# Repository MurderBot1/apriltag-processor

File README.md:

# AprilTag camera: custom vision chip + 120 fps global-shutter camera, one USB-C cable

A self-contained camera that detects AprilTags (tag36h11) at **1280x800 / 120 fps** and hands back the **camera's pose
in a world frame you define**. You send it the tags you use and where they are (plus the lens calibration) once; it
stores them in flash and then streams the camera position and orientation over the same USB-C cable that powers it.

```
OV9281 (MIPI, 120 fps) -> ECP5 LFE5U-25F FPGA running custom RTL (threshold, despeckle, labelling, frame streamer) -> 8-bit frame bus ->
                          RP2350 MCU (tag decoder in C, pose solve, USB, stored field map) -> host
```

Nothing here is a stock vision pipeline: the per-pixel work is **hardware designed in Verilog in this repo**, the per-tag work (sub-pixel
corner fitting, tag36h11 decoding) is C code in this repo that runs on the MCU on the binary frame the FPGA streams to it (architecture "A3",
`docs/costdown.md`; it started life as a custom FPGA processor, the TPU, kept in `ref/tpu` as the bit-exact reference). The host only sees the tag
estimates and poses, never an image.

## What is in the box

| directory | contents |
|---|---|
| `rtl/` | the chip: D-PHY + CSI-2 receiver, adaptive threshold, despeckle, connected components, the MCU frame streamer (`mask_stream`), SPI/I2C, top levels, pin constraints (`apriltag_cam.lpf`) |
| `tools/` | golden Python models of every block, TPU assembler + instruction-set simulator + the program (`tpu_prog.py`, the golden model of `firmware/core/attpu.c`), Cortex-M33 timing estimators (`m33_cycles.py`, `m33_pose_cycles.py`, `frame_budget.py`), Blender scene/dataset generator, reference detector, sensor init generator, FPGA flow scripts |
| `tb/`, `tests/` | Verilog testbenches and 226 pytest tests (see `docs/verification.md`) |
| `test_images/` | **100 rendered 1280x800 test frames in 10 categories of 10** (normal, bright, dark, low-contrast, gradient light, shadow, noise, clutter, blur, perspective; Blender Cycles, lens distortion + sensor noise model) with ground-truth poses (`ground_truth.json`) |
| `firmware/core`, `firmware/rp2350` | MCU firmware: pose solver, USB protocol, flash storage, auto exposure; RP2350 (Pico SDK) port |
| `host/` | Python library + CLI (`atcam.py`) with a simulated device so everything runs without hardware |
| `pcb/` | 4-layer 48 x 48 mm board generated from code (`design.py`, `build_pcb.py`), routed, fabrication outputs |
| `housing/` | 3D-printable two-part enclosure (OpenSCAD, STLs) |
| `docs/` | architecture, hardware, protocol, verification, FPGA results |
| `config/` | example field map (`tag_map.json`) and camera calibration |

## Using it

```python
import sys; sys.path.insert(0, "host")
from apriltag_cam import Camera, load_json
with Camera.open_serial("COM5") as cam:               # USB-C CDC serial port
    cam.set_calibration(load_json("config/camera_calibration.json"))
    cam.set_field(load_json("config/tag_map.json"))   # tag ids, sizes, 3D positions + orientations (quaternion wxyz)
    cam.commit()                                      # stored in flash; survives power cycles
    for pose in cam.stream():                         # ~120 Hz
        print(pose.frame_id, pose.position, pose.quaternion, pose.ntags, pose.rms_px)
```
`py -3.12 host/atcam.py --sim configure --map config/tag_map.json --calib config/camera_calibration.json` and `... --sim stream` run the same flow against the simulated device (native firmware + a fake FPGA fed with real RTL results).
Protocol: `docs/protocol.md`. Conventions (world, tag, camera frames, corner order) are at the top of `tools/geom.py`.

## Rebuilding / re-running

```
py -3.12 tools/make_tags.py               # tag images + the 587-code ROM table
py -3.12 tools/make_dataset_100.py        # the 100-image dataset: Blender renders (needs Blender 5.x) -> test_images/ (deterministic, see docs/verification.md)
py -3.12 tools/tpu_prog.py                # assemble the reference TPU program (ref/tpu/tpu_prog.hex)
py -3.12 tools/m33_cycles.py              # run time of the C tag unit on a Cortex-M33 (Unicorn + cycle model)
py -3.12 tests/run_all.py                 # the whole verification suite
bash tools/fpga_flow.sh                   # yosys + nextpnr-ecp5 (+ ecppack bitstream), default device 25k = shipping LFE5U-25F; FPGA_DEVICE=45k|85k for experiments
"C:/Program Files/KiCad/10.0/bin/python.exe" pcb/build_pcb.py --route ; py -3.12 pcb/make_outputs.py
```
Tools used: Icarus Verilog 13, Yosys 0.66, nextpnr-ecp5 0.7, KiCad 10, Freerouting 2.1, OpenSCAD 2021, Blender 5.1,
arm-none-eabi-gcc, Pico SDK (all installed during the build; see `docs/`).

## Build and release (deploy)

`bash tools/build_all.sh [--strict] [--skip-tests] [--skip-fpga]` builds every buildable output into `products/` (git-ignored) and writes
`products/MANIFEST.json` / `MANIFEST.txt` (commit, build date, tool versions, per-step ok/skipped/failed with notes, and file name, size and sha256).
Products: FPGA bitstream + netlist/config + timing/utilisation reports (yosys, nextpnr-ecp5, ecppack), RP2350 firmware (`.uf2/.elf/.bin`, needs
arm-none-eabi-gcc + Pico SDK via `PICO_SDK_PATH`), native firmware-sim library, host bundle + configs, Python wheel, C++ static lib + headers,
Java jar, Rust `.crate`/rlib, docs tarball and the committed PCB gerbers/BOM (copied, not regenerated; needs KiCad). A step whose toolchain is
missing is recorded as `skipped` in the manifest (never faked); set `REQUIRE="fpga firmware ..."` to make that an error. The FPGA flow targets the shipping part LFE5U-25F-8BG381I by default (nextpnr `--25k --package CABGA381 --speed 8`; `FPGA_DEVICE`/`FPGA_SPEED` override for experiments). The manifest has an `fpga` block (device, speed, package, part) and `fpga/summary.txt` states it. A timing miss for every seed in `FPGA_SEEDS`, or a bitstream for any other device or speed, is recorded as `failed` (the bitstream is still produced; `FPGA_ALLOW_NONSHIPPING=1` downgrades the device check to a warning for experiments).

**RP2350 firmware image.** Build on Linux (the Windows msys `ld` 2.47 fails the Pico SDK link with "pico_flash_region.ld appears multiple times", so
Windows is not a supported firmware build host). Needs `gcc-arm-none-eabi` (CI: Ubuntu 24.04 package, 13.2.1), `libnewlib-arm-none-eabi`, `cmake`, `ninja` and
Pico SDK **2.1.1** with submodules (tinyusb); the SDK builds picotool from source on first configure (network needed):
```
git clone --depth 1 --branch 2.1.1 --recurse-submodules --shallow-submodules https://github.com/raspberrypi/pico-sdk.git ~/pico-sdk
cmake -S firmware/rp2350 -B build/rp2350 -G Ninja -DPICO_SDK_PATH=~/pico-sdk && cmake --build build/rp2350
python3 tools/fw_size.py build/rp2350/apriltag_cam.elf --bin build/rp2350/apriltag_cam.bin --uf2 build/rp2350/apriltag_cam.uf2
```
The workflow `.github/workflows/firmware.yml` does this on every pull request that touches `firmware/`, checks the `.uf2` structure, uploads
`apriltag_cam.uf2/.elf/.bin/.elf.map` as the artifact `rp2350-firmware` and posts the size report (flash image vs 16 MB, static SRAM vs 520 KB) on the PR.
It never creates a release. Flash the `.uf2` by holding BOOTSEL while plugging in USB and copying the file to the `RP2350` drive (not yet tried on hardware).

**Releasing:** pushing to the `deploy` branch (`git push origin main:deploy`, or merge `main` into `deploy`) runs `.github/workflows/release.yml`.
It installs the toolchains, runs `tools/build_all.sh --strict`, uploads `products/` as a workflow artifact, and creates a NEW GitHub Release
tagged `deploy-<run_number>-<short sha>` with the products and manifest attached and notes listing the commit, date, tool versions and
build/test results. Earlier releases are never overwritten. `main` does not trigger releases. The workflow can also be started manually
(workflow_dispatch) from any ref; the manual run has a `dry_run` input (default true) that does everything except `gh release create`
(it still lists the assets and checks that `firmware_apriltag_cam.uf2/.elf` are present). A "Verify the build targets the shipping design" step fails the release unless the FPGA is 25k / CABGA381 / speed 8 with timing met, the uf2 exists, `products/docs/bom.csv` equals `pcb/output/bom.csv` with U1 = LFE5U-25F-8BG381I, and the committed PCB carries that part. It uses `GITHUB_TOKEN` with `contents: write`.

## Headline results (details and caveats in `docs/verification.md`, `docs/fpga.md`, `docs/hardware.md`)

* **120.08 fps** sustained in full-chip simulation at true sensor timing (832,800 clocks per frame at 100 MHz), every frame leaves the FPGA
  as a complete packet; the MCU has two frame buffers so capture never stalls.
* 100 rendered frames (10 conditions x 10, rendered for the shipping lens: CIL023, 82.2 degrees HFOV, fx 733 px, -5 % TV distortion) through the simulated chip + the MCU's solver: **median camera position error about
  1-5 mm and 0.03-0.17 deg per category** where tags are found; **88 % of the detectable tags overall (501 / 570; the reference AprilTag library: 98 %)**,
  100 % on dark / grad / noise / normal, 99 % bright, 92-94 % clutter / blur / persp, 90 % shadow, but still
  **2 % on the low-contrast category** with the reset THRESH ratio (54 / 54 with ratio 1, chosen automatically by the firmware), see `docs/verification.md`.
* GitHub Actions: one check per dataset category (`N/10 detected`, reference detector) plus an all-tests workflow, see `docs/verification.md`.
* RTL is verified bit-exact against Python golden models (threshold, despeckle, labelling), the C tag unit bit-exact against the golden model of the old FPGA processor, and the whole
  chain is exercised with real CSI-2 packets and a bit-level D-PHY model with lane skew and clock offsets.
* Open-source place-and-route onto the real ECP5 CABGA-381 pins, shipping part LFE5U-25F-8BG381I: 13.4 k LUT4 (55 %), 56 of 56 block RAM (100 %, no margin), core clock closes 85.7 MHz and D-PHY 200 MHz on 7 of 7 seeds (nextpnr estimates, not signoff; `docs/fpga.md`). Earlier 45F numbers (12.2 k LUT4, 56 of 108 block RAM, 4 of 6 seeds, older RTL and tools) are kept in `docs/fpga.md`, labelled as 45F.

## Honest limits - read before building hardware

1. **Not run on silicon.** Everything is simulated or tool-checked; there is no physical board. The ECP5 D-PHY receiver
   (LVDS gearing, sync hunt) and the OV9281 bring-up are the first things to validate on a prototype.
2. **OV9281 footprint**: the ball map comes from an open-hardware reference design, but the CSP ball pitch/pad size
   is assumed (0.5 mm / 0.25 mm). Verify against OmniVision's drawing before ordering. Bare-CSP assembly with an
   M12 holder needs a specialist assembler.
3. **Timing closure**: see `docs/fpga.md` for the measured fmax of each clock domain against the 100 MHz / 200 MHz
   targets. Anything reported as failing there must be fixed (more pipelining) before relying on 120 fps in hardware.
4. Detection is weaker than the reference library at long range (> ~3.5 m for 16.5 cm tags), for low-contrast scenes (0 % on the
   `lowcon` category with the reset THRESH ratio; 100 % with ratio 2, see `results/lowcon_ratio.md`) and for small / grazing / shadowed tags. The labeller no longer rejects busy frames (256 runs/row, label recycling,
   the 64 largest candidates kept), but a cluttered or noisy frame costs the MCU up to about 9 ms (estimate, Cortex-M33 emulation, median 1.6 ms; the old FPGA processor
   needed up to 30 ms): in a stream at 120 fps a heavy frame can make the MCU miss a packet (`frames_dropped`); the model predicts 1 - 4 % of frames
   if every 10th frame were the slowest of its category (`results/frame_budget.md`; the old design: 20 %). The MCU timing, the PIO/DMA frame
   capture and the bus timing margin are **not measured on hardware**.
5. No schematic capture: the board is netlist-first (`pcb/design.py`, `pcb/output/netlist.txt`).

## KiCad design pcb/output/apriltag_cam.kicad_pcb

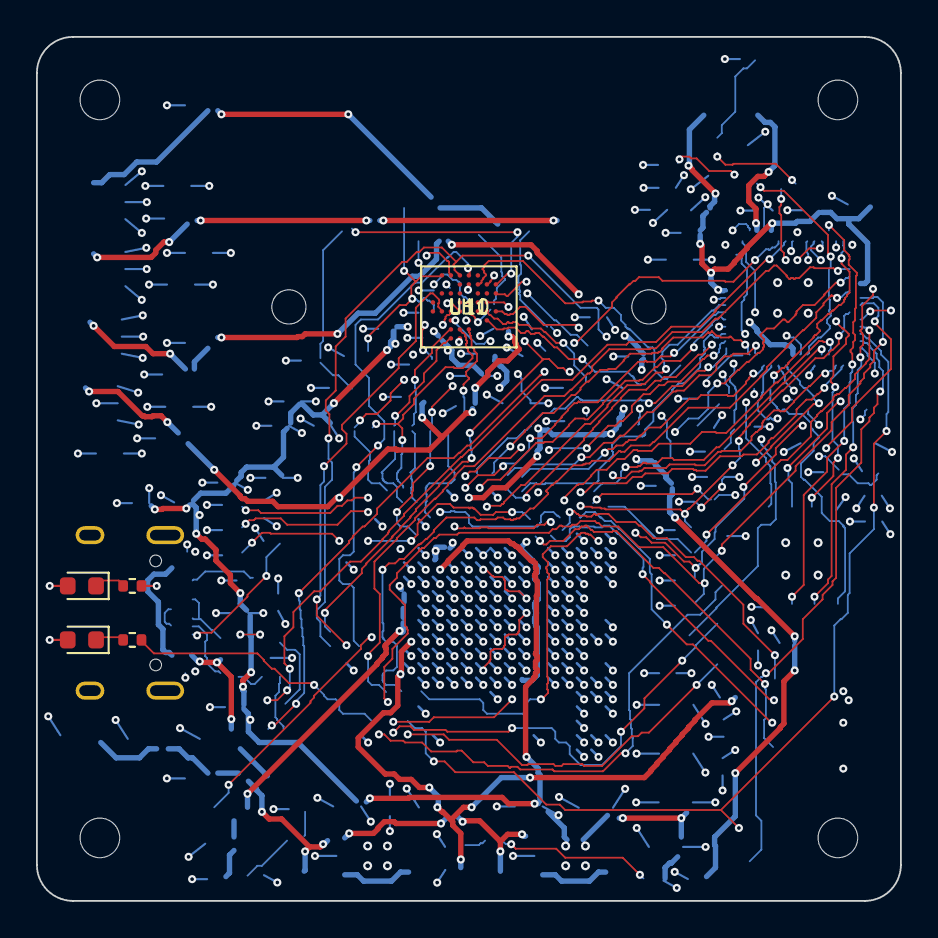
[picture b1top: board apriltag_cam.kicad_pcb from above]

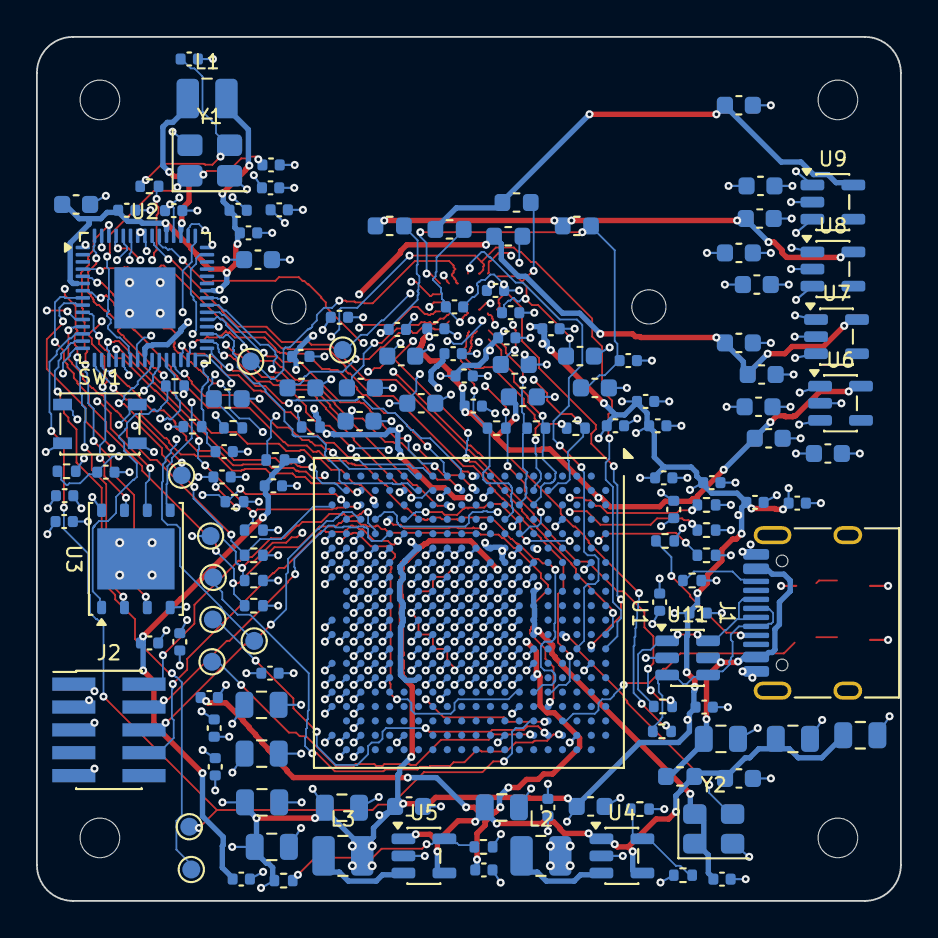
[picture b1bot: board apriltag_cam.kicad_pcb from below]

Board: 4 copper layers, 48.0 x 48.0 mm, 152 parts (142 on the bottom side), 95 nets.

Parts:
C1, C2, C3, C4, C5, C6, C7, C8, C9, C13, C14, C17, C38, C39, C40, C41, C42, C43, C44, C45, C46, C47, C48, C49, C50, C51, C52, C53, C54, C55, C56, C57, C58, C59, C60, C61, C62, C63, C64, C65, C70, C72, C74, C76, C77, C78: 100n; C_0402_1005Metric
C10, C11, C12, C36, C37, C66, C67, C68, C69: 4u7; C_0603_1608Metric
C15, C16: 15p; C_0402_1005Metric
C18, C19, C21, C24: 10u; C_0805_2012Metric
C20, C28, C30, C32, C34, C71, C73, C75, C79, C80, C81, C82: 1u; C_0603_1608Metric
C22, C23, C25, C26, C27: 22u; C_0805_2012Metric
C29, C31, C33, C35: 2u2; C_0603_1608Metric
D1: PWR; LED_0603_1608Metric
D2: STAT; LED_0603_1608Metric
FB1: BLM18 600R; L_0603_1608Metric
FB2, FB3, FB4, FB5, FB6: BLM18 120R; L_0603_1608Metric
J1: USB-C; USB_C_Receptacle_HRO_TYPE-C-31-M-12
J2: JTAG; PinHeader_2x05_P1.27mm_Vertical_SMD
L1: 3u3; L_1008_2520Metric
L2, L3: 2u2; L_1008_2520Metric
LH1: M12 holder 20x20; M12_LENS_MOUNT
MH1, MH2, MH3, MH4: M2; MountingHole_2.2mm_M2
R1, R2: 33R; R_0402_1005Metric
R3, R19, R20, R21, R22, R23: 10k; R_0402_1005Metric
R4, R5, R14, R15: 1k; R_0402_1005Metric
R6, R7: 5k1; R_0402_1005Metric
R8, R9: 27R; R_0402_1005Metric
R10: 453k; R_0402_1005Metric
R11, R13: 100k; R_0402_1005Metric
R12: 82k5; R_0402_1005Metric
R16, R17, R18: 4k7; R_0402_1005Metric
R24, R25, R26: 100R; R_0402_1005Metric
R27, R28: 2k2; R_0402_1005Metric
SW1: BOOTSEL; SW_SPST_PTS810
TP1: SWCLK; TestPoint_Pad_D1.0mm
TP2: SWDIO; TestPoint_Pad_D1.0mm
TP3: GND; TestPoint_Pad_D1.0mm
TP4: LED_1; TestPoint_Pad_D1.0mm
TP5: LED_2; TestPoint_Pad_D1.0mm
TP6: LED_3; TestPoint_Pad_D1.0mm
TP7: MCU_AUX; TestPoint_Pad_D1.0mm
TP8: FPGA_IRQ; TestPoint_Pad_D1.0mm
TP9: SNS_STROBE; TestPoint_Pad_D1.0mm
TP10: SNS_FSIN; TestPoint_Pad_D1.0mm
U1: LFE5U-25F-8BG381I; Lattice_caBGA-381_17x17mm_Layout20x20_P0.8mm
U2: RP2350A; QFN-60-1EP_7x7mm_P0.4mm_EP3.4x3.4mm
U3: W25Q128JVPIQ; WSON-8-1EP_6x5mm_P1.27mm_EP3.4x4.3mm
U4, U5: TLV62569; SOT-23-5
U6: ME6211C25; SOT-23-5
U7: TLV75518; SOT-23-5
U8: ME6211C28; SOT-23-5
U9: TLV75512; SOT-23-5
U10: OV9281; OV9281_CSP
U11: USBLC6-2SC6; SOT-23-6
Y1: 12MHz 10pF; Crystal_SMD_3225-4Pin_3.2x2.5mm
Y2: 24MHz 1.8V; Oscillator_SMD_Abracon_ASE-4Pin_3.2x2.5mm

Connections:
+1V1: C25.1, C26.1, C27.1, C38.1, C39.1, C40.1, C41.1, C42.1, C43.1, C44.1, C45.1, C46.1, C47.1, C48.1, C49.1, C66.1, C67.1, L3.2, R12.1, U1.H8, U1.H9, U1.H10, U1.H11, U1.H12, U1.H13, U1.J8, U1.J13, U1.K8, U1.K13, U1.L8, U1.L13, U1.M8, U1.M13, U1.N8, U1.N9, U1.N10, U1.N11, U1.N12, U1.N13
+1V1MCU: C7.1, C8.1, C9.1, C10.1, L1.2, U2.6, U2.23, U2.39, U2.50
+1V2: C35.1, FB3.1, FB5.1, U9.5
+1V8: C31.1, C37.1, C54.1, C55.1, C56.1, C57.1, C58.1, C70.1, FB4.1, R27.2, R28.2, U1.F9, U1.F10, U1.F11, U1.F12, U1.H6, U1.H7, U1.J6, U7.5, Y2.1, Y2.4
+2V5: C29.1, C50.1, C51.1, C52.1, C53.1, C68.1, U1.F6, U1.F15, U1.P6, U1.P15, U6.5
+2V8: C33.1, FB2.1, FB6.1, U8.5
+3V3: C1.1, C2.1, C3.1, C4.1, C5.1, C6.1, C11.1, C17.1, C22.1, C23.1, C28.1, C30.1, C32.1, C34.1, C36.1, C59.1, C60.1, C61.1, C62.1, C63.1, C64.1, C65.1, C69.1, D1.2, D2.2, J2.1, L2.2, R1.1, R2.1, R3.2, R10.1, R16.2, R19.2, R20.2, R21.2, R22.2, R23.2, U1.H14, U1.H15, U1.J15, U1.L6, U1.L7, U1.L14, U1.L15, U1.M6, U1.M15, U1.P9, U1.P10, U2.1, U2.11, U2.20, U2.30, U2.38, U2.45, U2.49, U2.53, U2.54, U3.8, U6.1, U6.3, U7.1, U7.3, U8.1, U8.3, U9.1, U9.3
+5V: C18.1, C20.1, C21.1, C24.1, FB1.2, U4.1, U4.4, U5.1, U5.4
ADC_AVDD: C13.1, R2.2, U2.44
AVDD_S: C71.1, C72.1, FB2.2, U10.B8
BOOT_N: R5.2, SW1.1
CC1: J1.A5, R6.1
CC2: J1.B5, R7.1
CFG0: R16.1, U1.U4
CFG1: R17.1, U1.T4
CFG2: R18.1, U1.R4
CLK24M: U1.D12, Y2.3
DOVDD_S: C75.1, C76.1, FB4.2, U10.B7
DVDD_S: C73.1, C74.1, FB3.2, U10.A2
EVDD_S: C78.1, FB6.2, U10.F3
FB_CLK: U1.K2, U2.36
FB_D0: U1.P1, U2.27
FB_D1: U1.N1, U2.28
FB_D2: U1.M1, U2.29
FB_D3: U1.L1, U2.31
FB_D4: U1.K1, U2.32
FB_D5: U1.P2, U2.33
FB_D6: U1.N2, U2.34
FB_D7: U1.L2, U2.35
FB_FS: U1.M3, U2.37
FPGA_CCLK: U1.U3, U2.18
FPGA_CFG_CS: U1.R2, U2.17
FPGA_CFG_MISO: U1.V2, U2.16
FPGA_CFG_MOSI: U1.W2, U2.19
FPGA_DONE: R21.1, U1.Y3, U2.12
FPGA_INITN: R20.1, U1.V3, U2.10
FPGA_IRQ: TP8.1, U1.F18, U2.13
FPGA_PROGRAMN: R19.1, U1.W3, U2.9
FPGA_RST: R22.1, U1.G16, U2.15
GND: C1.2, C2.2, C3.2, C4.2, C5.2, C6.2, C7.2, C8.2, C9.2, C10.2, C11.2, C12.2, C13.2, C14.2, C15.2, C16.2, C17.2, C18.2, C19.2, C20.2, C21.2, C22.2, C23.2, C24.2, C25.2, C26.2, C27.2, C28.2, C29.2, C30.2, C31.2, C32.2, C33.2, C34.2, C35.2, C36.2, C37.2, C38.2, C39.2, C40.2, C41.2, C42.2, C43.2, C44.2, C45.2, C46.2, C47.2, C48.2, C49.2, C50.2, C51.2, C52.2, C53.2, C54.2, C55.2, C56.2, C57.2, C58.2, C59.2, C60.2, C61.2, C62.2, C63.2, C64.2, C65.2, C66.2, C67.2, C68.2, C69.2, C70.2, C71.2, C72.2, C73.2, C74.2, C75.2, C76.2, C77.2, C78.2, C79.2, C80.2, C81.2, C82.2, J1.A1, J1.A12, J1.B1, J1.B12, J1.SH, J2.3, J2.5, J2.9, R6.2, R7.2, R11.2, R13.2, R14.2, R17.2, R18.2, SW1.2, TP3.1, U1.B7, U1.B14, U1.C19, U1.D4, U1.F7, U1.F8, U1.F13, U1.F14, U1.G4, U1.G6, U1.G7, U1.G8, U1.G9, U1.G10, U1.G11, U1.G12, U1.G13, U1.G14, U1.G15, U1.G17, U1.H19, U1.J2, U1.J7, U1.J9, U1.J10, U1.J11, U1.J12, U1.J14, U1.K6, U1.K7, U1.K9, U1.K10, U1.K11, U1.K12, U1.K14, U1.K15, U1.L9, U1.L10, U1.L11, U1.L12, U1.M2, U1.M7, U1.M9, U1.M10, U1.M11, U1.M12, U1.M14, U1.M16, U1.N6, U1.N7, U1.N14, U1.N15, U1.P7, U1.P8, U1.P11, U1.P12, U1.P13, U1.P14, U1.R19, U1.T6, U1.T7, U1.T8, U1.T9, U1.T10, U1.T11, U1.T12, U1.T13, U1.T14, U1.T15, U1.U6, U1.U7, U1.U8, U1.U9, U1.U10, U1.U11, U1.U12, U1.U13, U1.U14, U1.U15, U1.V5, U1.V6, U1.V7, U1.V8, U1.V9, U1.V10, U1.V11, U1.V12, U1.V13, U1.V14, U1.V15, U1.V16, U1.V17, U1.V18, U1.V19, U1.V20, U1.W6, U1.W7, U1.W12, U1.W15, U1.W16, U1.W19, U1.W20, U1.Y5, U1.Y6, U1.Y7, U1.Y8, U1.Y11, U1.Y12, U1.Y14, U1.Y15, U1.Y16, U1.Y17, U1.Y19, U2.47, U2.61, U3.4, U3.9, U4.2, U5.2, U6.2, U7.2, U8.2, U9.2, U10.A3, U10.C8, U10.E3, U11.2, Y1.2, Y1.4, Y2.2
JTAG_TCK: J2.4, U1.T5
JTAG_TDI: J2.8, U1.R5
JTAG_TDO: J2.6, U1.V4
JTAG_TMS: J2.2, U1.U5
LED_1: TP4.1, U1.D19
LED_2: TP5.1, U1.E19
LED_3: TP6.1, U1.F19
LED_PWR_K: D1.1, R14.1
LED_STAT: R15.1, U1.D18
LED_STAT_K: D2.1, R15.2
MCU_AUX: TP7.1, U2.14
MCU_RUN: C14.1, R3.1, U2.26
MIPI_CLK_N: R24.2, U1.E2, U10.H4
MIPI_CLK_P: R24.1, U1.F2, U10.G4
MIPI_D0_N: R25.2, U1.F3, U10.H3
MIPI_D0_P: R25.1, U1.G3, U10.G3
MIPI_D1_N: R26.2, U1.G5, U10.F5
MIPI_D1_P: R26.1, U1.H4, U10.G5
PVDD_S: C77.1, FB5.2, U10.D5
QSPI_SCLK: U2.56, U3.6
QSPI_SD0: U2.57, U3.5
QSPI_SD1: U2.59, U3.2
QSPI_SD2: U2.58, U3.3
QSPI_SD3: U2.55, U3.7
QSPI_SS: R5.1, U2.60, U3.1
SCL: R27.1, U1.A12, U10.E4
SDA: R28.1, U1.A13, U10.A4
SNS_FSIN: TP10.1, U10.B5
SNS_STROBE: TP9.1, U10.B6
SPI_CS: R23.1, U1.E17, U2.8
SPI_MISO: U1.F16, U2.7
SPI_MOSI: U1.E18, U2.5
SPI_SCK: U1.E16, U2.4
SW1V1: L3.1, U5.3
SW1V1_FB: R12.2, R13.1, U5.5
SW3V3: L2.1, U4.3
SW3V3_FB: R10.2, R11.1, U4.5
SWCLK: TP1.1, U2.24
SWDIO: TP2.1, U2.25
USB_DM_MCU: R9.2, U2.51
USB_DN: J1.A7, J1.B7, R9.1, U11.3, U11.4
USB_DP: J1.A6, J1.B6, R8.1, U11.1, U11.6
USB_DP_MCU: R8.2, U2.52
VBUS: C19.1, FB1.1, J1.A4, J1.A9, J1.B4, J1.B9, U11.5
VH: C79.1, U10.E8
VN1: C80.1, U10.D7
VN2: C81.1, U10.E7
VN3: C82.1, U10.F7
VREG_AVDD: C12.1, R1.2, U2.46
VREG_LX: L1.1, U2.48
XIN: C15.1, U2.21, Y1.1
XOUT: C16.1, R4.1, Y1.3
XOUT_R: R4.2, U2.22
XSHUTDN: U1.C13, U10.A5
XVCLK: U1.B13, U10.E2

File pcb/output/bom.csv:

Qty,Value,Footprint,References
46,100n,C_0402_1005Metric,C1 C2 C3 C4 C5 C6 C7 C8 C9 C13 C14 C17 C38 C39 C40 C41 C42 C43 C44 C45 C46 C47 C48 C49 C50 C51 C52 C53 C54 C55 C56 C57 C58 C59 C60 C61 C62 C63 C64 C65 C70 C72 C74 C76 C77 C78
9,4u7,C_0603_1608Metric,C10 C11 C12 C36 C37 C66 C67 C68 C69
2,15p,C_0402_1005Metric,C15 C16
4,10u,C_0805_2012Metric,C18 C19 C21 C24
12,1u,C_0603_1608Metric,C20 C28 C30 C32 C34 C71 C73 C75 C79 C80 C81 C82
5,22u,C_0805_2012Metric,C22 C23 C25 C26 C27
4,2u2,C_0603_1608Metric,C29 C31 C33 C35
1,PWR,LED_0603_1608Metric,D1
1,STAT,LED_0603_1608Metric,D2
1,BLM18 600R,L_0603_1608Metric,FB1
5,BLM18 120R,L_0603_1608Metric,FB2 FB3 FB4 FB5 FB6
1,USB-C,USB_C_Receptacle_HRO_TYPE-C-31-M-12,J1
1,JTAG,PinHeader_2x05_P1.27mm_Vertical_SMD,J2
1,3u3,L_1008_2520Metric,L1
2,2u2,L_1008_2520Metric,L2 L3
2,33R,R_0402_1005Metric,R1 R2
1,453k,R_0402_1005Metric,R10
2,100k,R_0402_1005Metric,R11 R13
1,82k5,R_0402_1005Metric,R12
3,4k7,R_0402_1005Metric,R16 R17 R18
3,100R,R_0402_1005Metric,R24 R25 R26
2,2k2,R_0402_1005Metric,R27 R28
6,10k,R_0402_1005Metric,R3 R19 R20 R21 R22 R23
4,1k,R_0402_1005Metric,R4 R5 R14 R15
2,5k1,R_0402_1005Metric,R6 R7
2,27R,R_0402_1005Metric,R8 R9
1,BOOTSEL,SW_SPST_PTS810,SW1
1,LFE5U-25F-8BG381I,Lattice_caBGA-381_17x17mm_Layout20x20_P0.8mm,U1
1,USBLC6-2SC6,SOT-23-6,U11
1,RP2350A,QFN-60-1EP_7x7mm_P0.4mm_EP3.4x3.4mm,U2
1,W25Q128JVPIQ,WSON-8-1EP_6x5mm_P1.27mm_EP3.4x4.3mm,U3
2,TLV62569,SOT-23-5,U4 U5
1,ME6211C25,SOT-23-5,U6
1,TLV75518,SOT-23-5,U7
1,ME6211C28,SOT-23-5,U8
1,TLV75512,SOT-23-5,U9
1,12MHz 10pF,Crystal_SMD_3225-4Pin_3.2x2.5mm,Y1
1,24MHz 1.8V,Oscillator_SMD_Abracon_ASE-4Pin_3.2x2.5mm,Y2

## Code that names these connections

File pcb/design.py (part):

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        fn = io_tab[ball][2]
        if fn == 'D0/MOSI/IO0': ball_net[ball] = 'FPGA_CFG_MOSI'
        elif fn == 'D1/MISO/IO1': ball_net[ball] = 'FPGA_CFG_MISO'
        elif fn.startswith('HOLDN/DI/BUSY/CSSPIN'): ball_net[ball] = 'FPGA_CFG_CS'
fpga_nets = {b: n for b, n in ball_net.items()}
add('U', 'Package_BGA', 'Lattice_caBGA-381_17x17mm_Layout20x20_P0.8mm', 'LFE5U-25F-8BG381I', FPGA_POS[0], FPGA_POS[1], 0, 'bottom',
    fpga_nets, ref_='U1', note='Lattice ECP5-25F (custom RTL: CSI-2/D-PHY RX, threshold, despeckle, CCL, frame bus to the MCU)')

# ---------------------------------------------------------------------------------------------- MCU U2 (RP2350A)
mcu_pin_tab = json.load(open(os.path.join(HERE, 'rp2350a_pins.json')))              # [number, name, type]
MCU_GPIO = {'GPIO2': 'SPI_SCK', 'GPIO3': 'SPI_MOSI', 'GPIO4': 'SPI_MISO', 'GPIO5': 'SPI_CS', 'GPIO6': 'FPGA_PROGRAMN',
            'GPIO7': 'FPGA_INITN', 'GPIO8': 'FPGA_DONE', 'GPIO9': 'FPGA_IRQ', 'GPIO10': 'MCU_AUX', 'GPIO11': 'FPGA_RST',
            'GPIO12': 'FPGA_CFG_MISO', 'GPIO13': 'FPGA_CFG_CS', 'GPIO14': 'FPGA_CCLK', 'GPIO15': 'FPGA_CFG_MOSI',
            **{f'GPIO{16 + i}': f'FB_D{i}' for i in range(8)}, 'GPIO24': 'FB_CLK', 'GPIO25': 'FB_FS'}
MCU_OTHER = {'IOVDD': '+3V3', 'DVDD': '+1V1MCU', 'XIN': 'XIN', 'XOUT': 'XOUT_R', 'SWCLK': 'SWCLK', 'SWDIO': 'SWDIO', 'RUN': 'MCU_RUN',
             'ADC_AVDD': 'ADC_AVDD', 'VREG_AVDD': 'VREG_AVDD', 'VREG_PGND': 'GND', 'VREG_LX': 'VREG_LX', 'VREG_VIN': '+3V3',
             'VREG_FB': '+1V1MCU', 'USB_DM': 'USB_DM_MCU', 'USB_DP': 'USB_DP_MCU', 'USB_OTP_VDD': '+3V3', 'QSPI_IOVDD': '+3V3',
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res('10k', 'MCU_RUN', '+3V3', mx + 3.0, my - 5.6)
cap('100n', 'MCU_RUN', mx + 4.6, my - 5.6)
# 12 MHz crystal, CL = 10 pF (ABM8-272-T3).  Load seen by the crystal = C15*C16/(C15+C16) + Cstray = 15*15/30 + ~3 = 10.5 pF.
add('Y', 'Crystal', 'Crystal_SMD_3225-4Pin_3.2x2.5mm', '12MHz 10pF', mx - 0.5, my + 8.6, 0, 'bottom', {'1': 'XIN', '2': 'GND', '3': 'XOUT', '4': 'GND'})
cap('15p', 'XIN', mx - 2.8, my + 6.8)
cap('15p', 'XOUT', mx + 1.8, my + 6.8)
res('1k', 'XOUT', 'XOUT_R', mx - 0.5, my + 6.2)
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
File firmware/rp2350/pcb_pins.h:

/* RP2350 pin assignments for the AprilTag camera board.
 *
 * !! PROVISIONAL !!  The GPIO numbers below are the working assumption of the firmware team; the PCB engineer must confirm
 * (or change) them against the schematic.  Every pin used by the firmware is listed here and ONLY here.
 *
 *  Signal              GPIO  Function      Direction (MCU)  Connects to
 *  ------------------  ----  ------------  ---------------  -------------------------------------------------------
 *  FPGA_SPI_SCK         2    SPI0 SCK      out              FPGA spi_slave sck   (mode 0, <= 12 MHz)
 *  FPGA_SPI_MOSI        3    SPI0 TX       out              FPGA spi_slave mosi
 *  FPGA_SPI_MISO        4    SPI0 RX       in               FPGA spi_slave miso  (FPGA tri-states when CS high)
 *  FPGA_SPI_CSN         5    SIO (GPIO)    out, idle high   FPGA spi_slave cs_n   (driven by software, not the SPI block)
 *  FPGA_PROGRAMN        6    SIO           out, idle high   ECP5 PROGRAMN  (low pulse restarts configuration)
 *  FPGA_INITN           7    SIO           in, pull-up      ECP5 INITN     (open drain, high = ready for bitstream)
 *  FPGA_DONE            8    SIO           in, pull-up      ECP5 DONE      (high = configured)
 *  FPGA_IRQ             9    SIO           in               FPGA result-ready / frame-done (optional, polled today)
 *  LED_STAT            10    SIO           out              status LED
 *  FB_D0..FB_D7        16-23 PIO0          in               FPGA frame bus data (rtl/mask_stream.v mcu_d[0..7]); D0 must be the PIO IN base
 *  FB_CLK              24    PIO0          in               FPGA frame bus strobe (mcu_clk) = IN base + 8
 *  FB_FS               25    SIO           in (IRQ)         FPGA frame bus packet-valid level (mcu_fs)
 *  FPGA_CFG_SCK        14    SPI1 SCK      out              ECP5 CCLK   (slave SPI configuration port)
 *  FPGA_CFG_MOSI       15    SPI1 TX       out              ECP5 MOSI   (SI)
 *  FPGA_CFG_MISO       12    SPI1 RX       in               ECP5 MISO   (SO)
 *  FPGA_CFG_CSN        13    SIO           out, idle high   ECP5 CSSPIN / SN
 *  BOOT button         --    BOOTSEL       in               dedicated QSPI_SS pin, not a GPIO (used only by the boot ROM)
 *
 * SPI1 pin function check (RP2350): GPIO12 = SPI1 RX, GPIO13 = SPI1 CSn (used as plain GPIO here), GPIO14 = SPI1 SCK,
 * GPIO15 = SPI1 TX.  SPI0: GPIO2 = SCK, GPIO3 = TX, GPIO4 = RX, GPIO5 = CSn (plain GPIO here).
 */
#pragma once

#define PIN_FPGA_SPI_SCK    2
#define PIN_FPGA_SPI_MOSI   3
#define PIN_FPGA_SPI_MISO   4
#define PIN_FPGA_SPI_CSN    5
#define PIN_FPGA_PROGRAMN   6
#define PIN_FPGA_INITN      7
#define PIN_FPGA_DONE       8
#define PIN_FPGA_IRQ        9
#define PIN_LED_STAT        10
#define PIN_FB_D0           16     /* ... PIN_FB_D0 + 7 = 23 */
#define PIN_FB_CLK          24     /* must equal PIN_FB_D0 + 8: frame_rx.pio waits on 'pin 8' */
#define PIN_FB_FS           25
#define PIN_FPGA_CFG_SCK    14
#define PIN_FPGA_CFG_MOSI   15
#define PIN_FPGA_CFG_MISO   12
#define PIN_FPGA_CFG_CSN    13

#define FPGA_SPI_INST       spi0
#define FPGA_SPI_HZ         (12u * 1000u * 1000u)     /* rtl/spi_slave.v: SCK <= clk/6 (16 MHz at 100 MHz) */
#define FPGA_CFG_SPI_INST   spi1
#define FPGA_CFG_SPI_HZ     (25u * 1000u * 1000u)     /* ECP5 slave SPI: up to 60 MHz; keep margin for the board */

/* Flash layout (16 MB QSPI):
 *   0x000000 - 0x0FFFFF   firmware image (1 MB)
 *   0x100000 - 0x3FFFFF   FPGA bitstream partition (3 MB, header + raw .bit, see fpga_config.h)
 *   0xFFE000 - 0xFFFFFF   two 4 KB configuration slots (field map + calibration), see hal_flash.c
 */
#define FLASH_TOTAL_BYTES        (16u * 1024u * 1024u)
#define FLASH_BITSTREAM_OFFSET   0x00100000u
#define FLASH_BITSTREAM_MAX      0x00300000u
#define FLASH_CONFIG_OFFSET      (FLASH_TOTAL_BYTES - 2u * 4096u)
